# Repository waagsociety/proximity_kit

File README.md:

# Proximity Kit

This repo contains the documentation of the following projects:

* PK_MUV, developed as part of deliverable for the prject [MUV](https://www.muv2020.eu/)

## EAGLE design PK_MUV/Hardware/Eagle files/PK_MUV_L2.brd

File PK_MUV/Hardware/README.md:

# Parts
The PK_MUV kit is a portable device made of the following parts and features:

* Mcu/WiFi: Adafruit Feather HUZZAH esp8266 board
* NFC Reader: RC522 NFC reader
* Visual feedback: 3 WS1282 LEDs
* Audio feedback: buzzer
* Power switch
* Reset button
* Configuration button
* Indicator RGB Led for battery status
* Indicator RGB Led for configuration mode
* Indicator RGB Led for feedback
* Power supply: rechargeable battery or micro USB cable
* 6 mounting holes

The PK_MUV uses two off-the-shelf boards, the [Adafruit Feather HUZZAH esp8266](https://learn.adafruit.com/adafruit-feather-huzzah-esp8266/overview) and the NFC reader breakout board based on [MFRC522 chip](https://www.nxp.com/docs/en/data-sheet/MFRC522.pdf), and four boards made in the fablab, the PK_MUV pcb, the PK_MUV_L1 pcb, the PK_MUV_L2 pcb and the PK_MUV_sw pcb.

The boards are made using the small milling machine Roland Modela MDX-20, each pcbs require two jobs: mill the trace and cut/drill the boards, in the folder digital files you find the png machinable files.
Tools used:
- one side copper plate, FR1
- to mill the traces: endmill, 1/64inch diameter
- to cut and drill: endmill, 1/32inch diameter

The files used on the machine are in the folder [Machinable files](https://github.com/emmapa/proximity_kit/tree/master/PK_MUV/Tech/Machinable%20files).<br>
The original Eagle files are in the [Eagle files](https://github.com/emmapa/proximity_kit/tree/master/PK_MUV/Tech/Eagle%20files).

In Fablab Amsterdam the software to generate the rml file and send it to the machine is Fabmodules. It is highly recommended to use the last version of Fabmodules, aka mods http://mods.cba.mit.edu/; previous versions of fabmodules, still work but double check the output of the software before to send the job to the machine, in some cases the path is not well calculated.

In the image below you find the setting to engrave the traces, drill holes and cutout the board.
<br>

Note: when you mill the outlines, you will need to trick the fabmodules!! Some holes are two smalls to be identified with a diameter tool of 1/64inch (0.79248mm) so you can set the diameter tool to 0.78mm and all the holes will be milled; yes, you lose some copper on the pad but it is still enough to solder vias and components.

#### PK_MUV pcb

| top view  | bottom view |
| ------------- | ------------- |
|   |  |
| All the header are THT, pitch 2.54mm. <br> JP_LEDS: 1x3 female header, THT <br> JP_BUZ: holes for piezo<br> JP_SW: 2x2 male header<br> Feather header 1: 1x16 female header<br> Feather header 2: 1x16 female header<br> JP_LED_TAG: 1x4 female header<br> JP_NFC: 1x8 female header <br> | All the resistors are smd 1206. <br>R1: 1M Ohm<br> R2: 220k Ohm<br> R3: 0 Ohm<br> R4: 0 Ohm<br> R5: 10k Ohm<br> R6: 470 Ohm <br> R7: 0 Ohm<br>|
|   | |
|| 

**note**: the red traces are jumper wires placed on the top layer

#### PK_MUV_L1 pcb

| top view  | bottom view |
| ------------- | ------------- |
|   |  |
| The header is THT, pitch 2.54mm. <br> JP1: 1x04 male header 90° | Capacitors is smd 1206. <br>C1: 0.1uF <br> U1: WS2812B Led|
|   | |
|   | |

#### PK_MUV_L2 pcb

| top view  | bottom view |
| ------------- | ------------- |
|   |  |
| The header is THT, pitch 2.54mm. <br> JP1: 1x03 male header 90°   | Resistors and capacitors are smd 1206. <br>C1=C2: 0.1uF <br> U1=U2: WS2812B Led |
|   | |
|   | |

#### PK_MUV_sw pcb

| top View  | bottom view |
| ------------- | ------------- |
|   |  |
| sw1 = sw2: Tactile Switch THT | The header is smd, pitch 2.54mm <br> JP1: 2x2 male header<br> |
|   | |
||  |

### Battery cable
The switch power is inserted in the power wire of the battery.

Depending on the size of the case and the arrangements inside it, you could need to extend the power cable. This [tutorial](https://learn.adafruit.com/on-slash-off-switches) explains step-by-step how to wire the on/off switch, the material are part of the BOM.

### Assembly notes
#### Buzzer
On the PK_MUV pcb there two holes dedicated to the transducer element, depending on the model and the wires,  you can use both THT pads or just one.

#### Switches
The connection of the switches to the main board happens with two IDC connectors and a four wires flat cable.
It is important to plug the connectors in the right orientation, in the photos below you can see the alignment between the two boards.

#### General overview
The PK_MUV uses female/male header to attach the different boards but it works also using different settings.
You could solder all the components directly on the PK_MUV board to have a more compact and robust solution.
You could also use jumper wires to place the pcb far from the main pcb.

### BOM notes
Many items in the BOM can be bought only in minimum amount, when you actually are going to use one or two component. The total cost is therefore expressed as:
* total purchase: the cost of the purchase, buying the minimum amount per items
* cost of 1 kit: considering the cost of only the component used in the kit.

for example: if you buy the "feather header 1" from Farnell, you have to buy 10 components even if you are going to use only one. In the purchase cost the item "feather header 1" is 12€ but in the single cost of one kit, the item value is 1,2€.

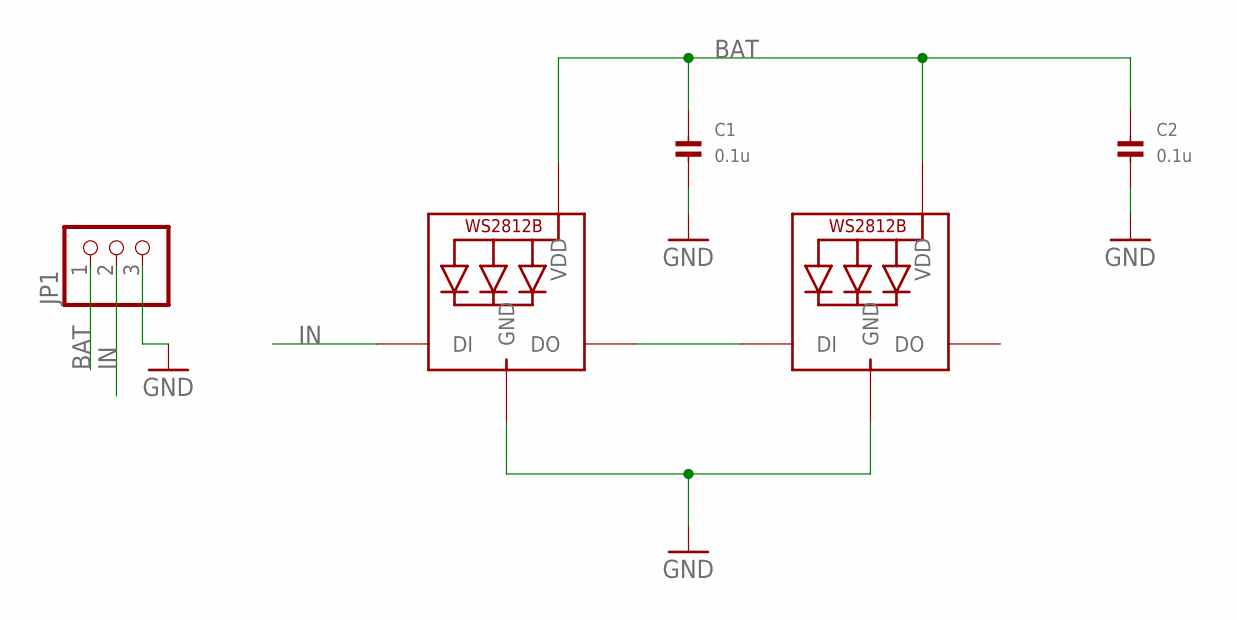
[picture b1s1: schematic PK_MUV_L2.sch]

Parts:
C1, C2: 0.1u; 1206
JP1: HEADER-1X3; 1X03_OVAL
LED1, LED2: WS2812B_5050N; WS2812B-NARROW

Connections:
BAT: C1.1, C2.1, JP1.1, LED1.1-VDD (VDD), LED2.1-VDD (VDD)
GND: C1.2, C2.2, JP1.3, LED1.3-GND (GND), LED2.3-GND (GND)
IN: JP1.2, LED1.4-DIN (DI)
unnamed: LED1.2-DOUT (DO), LED2.4-DIN (DI)

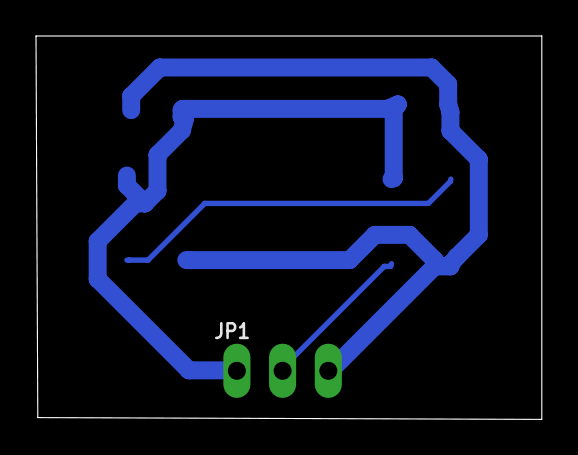
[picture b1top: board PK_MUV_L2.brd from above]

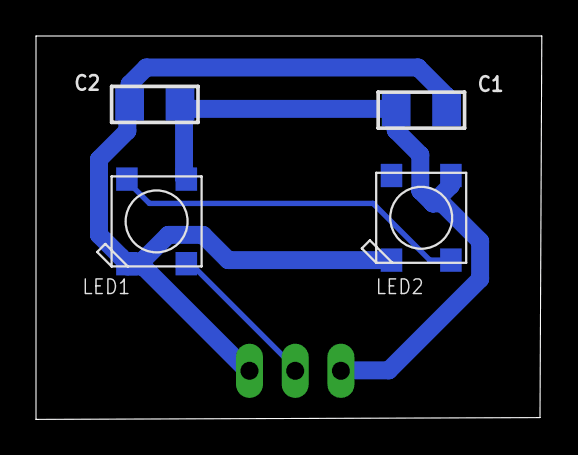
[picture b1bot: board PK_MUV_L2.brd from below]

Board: 2 copper layers, 28.1 x 21.3 mm, 5 parts (4 on the bottom side), 4 nets.

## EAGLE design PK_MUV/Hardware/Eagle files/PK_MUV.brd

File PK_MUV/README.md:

# PK_MUV

This page contains the description of the PK_MUV kit and the instructions to use it.<br>
In the Repo you also find:
* blocks diagram
* digital files to reproduce it, Eagle file and png files
* code
* BOM

The kit described in this Repo is about the electronics components and the firmware to realise the PK_MUV.

## Intro
The goal of the kit is to enable users of the application MUV, to identify proximity to strategic locations or routes, where the PK_MUV is located. The detection of proximity uses NFC technology and the user must be in possession of a [Tag_MUV](MUV-Tags) to properly use this feature of the app.
The PK_MUV is the device where the user can register proximity and it can be located in places important for the MUV project, for example: schools, offices, shops, parks, public services.

The PK_MUV is a WiFi module (esp8266) with NFC reader (RC522).
The PK_MUV kit is programmed to read [Tag_MUV](MUV-Tags). When the user operates the TAG_MUV on PK_MUV kit, the following informations are sent to the MUV server:
* Tag_MUV UID to identify the user
* PK_MUV ID to identify the location of the kit.<br>

The kit includes:
- Power slide switch: to turn on/off the kit when it runs on battery
- Reset switch: to reset the kit while it is operating
- Config switch: it is used to enter in configuration mode or run the check routine.
- Tag Led: rgb Led that gives feedback when a tag is detected by the reader, also called Tag routine.
- Config Led: rgb Led that gives feedback during the start-up and the check routines.
- Batt Led: rgb Led that visualise the battery status.

### Connect the PK_MUV to the local WiFi
Turn on the PK_MUV (ON/OFF switch). If the kit is not connected to the WiFi, the Config Led is on/blue, the kit is ready to be connected and it creates a network named MUV.
At this point you need a smartphone/tablet or computer, join the network MUV.

|| |
| ------------- | ------------- |

Automatically on the device you are using (smartphone/tablet/computer) the configuration window will pop-up.

|| |
| ------------- | ------------- |

If the window doesn't appear, open a browser and go to the address: http://192.168.4.1/.

Clicking on Info, you can see the information related to the kit and find the PK_MUV kit ID that in the window is called Chip ID.

Clicking on Configure WiFi, you are in the right place to connect the kit to you local WiFi.

Select the WiFi and type the password.
In the tag "Insert address", write the location of the kit.

Click save and the kit will be now connected, the Config Led blinks green and you are ready to use the kit.
It is also possible to enter in configuration mode manually, see the below section [configuration mode](Configuration-Mode).

### Modes and Routines/Messages
The operation of the PK_MUV can be described by modes and routine.
The modes are conditions in which the kit is waiting for some actions from the users:
* **configuration mode**: the kit is waiting to be connected to the local WiFi
* **operation mode**: the kit is operating and waiting to detect a Tag_MUV

The routines are a set of actions that the kit executes when it is triggered:
* **start-up routine**: it happens when the kit is powered-on or reset
* **tag routine**: it happens when the kit detect a tag
* **check routine**: it happens when the user need to check the functionality of the kit
The
<br>

#### Configuration Mode
Config Led : <br>
The kit is in configuration mode when it is not connected to the Local WiFi. In configuration mode the Config Led is steady blue.
You can manually enter in configuration mode with the following steps: keep pushed the Config switch and reset the kit. Hold the Config switch until the Config Led turns blue, the PK_MUV can to connected to the local Wifi, see previous [section](Connect-the-PK-MUV-to-the-local-WiFi).

**note**: you can also use configuration mode to change the WiFi Network at which the PK_MUV is connected.

#### Operation Mode
Config Led: <br>
If the kit has been successfully configured, it enters in operation mode.
The Tag Led and the Config Led are off, the NFC reader is ready to accept tags and the WiFi module is off to optimise the power consumption.
When the kit is operating and it has not been triggered by any tag, it will stay in operation mode.

#### Start-up routine
Config Led: <br>
When the kit is powered-on or reseted, it runs a sequence of test to verify the proper functionality.
It will connect to the local WiFi, it will verify the connection with the server MUV and it will send a start-up message. If the execution of the start-up routine is successful the Config Led blinks green light and the start-up message is sent to the MUV server:

{"message":"startup","id":1756474,"location":"Nieuwmarkt 4, Amsterdam","rssi":-52, "batt":50}

for details about the payload content, see [Uplinks](https://github.com/waagsociety/proximity_kit/tree/master/PK_MUV/Software#Uplinks).

#### Tag Routine
Tag Led : <br>
When the reader get a Tag_MUV, the Tag Led blinks three times, meaning:
* the kit received a tag and the tag is recognised as Tag_MUV
* the kit connected to the local WiFi
* the kit sent the MUV message to the MUV server

and the kit will send to the MUV the following payload:

{"id":1756474,"uid":"04:23:AB:32:EC:4C:81”}

for details about the payload content, see [Uplinks](https://github.com/waagsociety/proximity_kit/tree/master/PK_MUV/Software#Uplinks).

The color code of the Tag Led is:<br>
 : the tag doesn't have the credential of the MUV project.<br>
 : the tag was recognised as MUV, but the kit couldn't connect to the WiFi.<br>
 : the tag was recognised as MUV, it could connect to the WiFi but it couldn't reach the MUV server.

#### Check Routine
To execute the check routine, press once the Config Switch and you can verify the following features:
* battery level
* WiFi connection
* MUV server connectivity

The Batt Led will be steady for few seconds and the colour represents the battery level.<br>
The feedback of the routine is visualised on the Config Led:<br>
: the kit is operating properly and it will send the "check message".<br>
: the kit can't connect to the WiFi.<br>
: the kit can't reach the MUV server and the "check message" is not sent.

The message sent to the server is:<br>
{"message":"check","id":1756474,"location":"Nieuwmarkt 4, Amsterdam","rssi":-59,"batt”:50}<br>
for details about the payload content, see [Uplinks](https://github.com/waagsociety/proximity_kit/tree/master/PK_MUV/Software#Uplinks).

## Power supply and Battery Led
The PK_MUV kit runs on a rechargeable battery, a 2000mAh Lithium Ion Polymer cell last about 4 days when the PK_MUV kit works in operational mode. The status of the battery is visualised by the Batt Led:

* battery level >= 96%: Batt Led is steady on, green
* 20% > battery level >= 10%: Batt Led blinks, colour red.
* battery level < 10%: Batt Led is steady on, colour red.

When the battery is between 96% and 20%, the Batt Led stays off, and to know its level you need to execute the Check Routine. Colour scale used during Check routine:
*  100% > battery level >= 80%: Batt Led colour green
*  80% > battery level >= 60%: Batt Led green/yellow
*   60% > battery level >= 40%: Batt Led yellow.
*   40% > battery level >= 20%: Batt Led orange.
*  20%  battery level >= 0: Batt Led colour red.

When the Batt Led is red, the battery is almost empty. To recharge the internal battery you can use a micro USB cable and a +5V USB charger (the ones you use with phones are good), plug the cable to the USB port on the side of the kit. When the Batt Led is steady green, the battery is charged. While the kit is under charge, it still operates normally.

**Note**: when you charge the battery, be sure the power switch is ON otherwise the battery will not get charged.

You can run the PK_MUV kit without battery and use the USB cable to supply it. In this case it is recommended to disconnect the battery or leave the power switch in position OFF. In this setting, the Batt Led is steady off.<br>
**Note**: when the USB cable is plugged, the kit operated continuously.

## MUV Tags
The Tags that have been successfully tested are NTAG213 and NTAG203, they are manufactured in different shapes: key-chain, sticker, business card and bracelet.<br>
<p align="center">

 <br></p>
To be able to use a Tag with the PK_MUV kit, you have to write in the Tag the MUV password and transform it in a Tag_MUV. On [this page](https://www.wakdev.com/en/apps.html) you find a list of apps to write NFC Tags but you also need a device to actually write the tag; in some cases the phone can do the job but in some other cases, for example if you have an iPhone6, you have to adopt an external device. During the testing phase of the PK_MUV, the ACR122 writer has been used with the desktop version of the software NFC tools.

How to use the ACR122 with NFC tools: [link](https://www.wakdev.com/en/apps/nfc-tools-pc-mac.html) To have access to the key, see section [Contacts](Contacts).

## Known Issues

There are some known issues we are working on to improve the case:

- USB hole in case is not large enough for many sizes of USB connector
- The USB port could be closer to the wall of the case
- The buttons should be press fit into the case so that no glue is required
- There should be letters engraved above the buttons to be able to tell which one is which
- There should be 2 acrylic diffusers on the back side for the LEDs, one for each LED
- The NFC sensor should be moved as close to the front wall as possible to improve the connection when the battery is low.

## Troubleshooting
| Problem | Solution |
|---------| -------- |
| Config Led is on: purple <br> | The FS are formatted and The WiFi settings reseted. <br> The Feather esp8266 must be reprogrammed.  <br>See [Code](code) page. |
| Config Led is on: aqua <br> | The MUV server can't be reached. <br> Reset the Kit. <br> Check the MUV credentials saved in the code |
| Config Led is on: blue <br>  | The kit is in Configuration mode.<br> Ready to be connected to the Local WiFi: [how](#Connect-the-PK-MUV-to-the-local-WiFi)  |

## Contacts
To have access to the MUV password, please contact: stefano@waag.org <br>
If you have questions about the reproducion or making or code, you can use the issue format of the repo.

<br />This work is licensed under a <a rel="license" href="http://creativecommons.org/licenses/by-sa/4.0/">Creative Commons Attribution-ShareAlike 4.0 International License</a>.

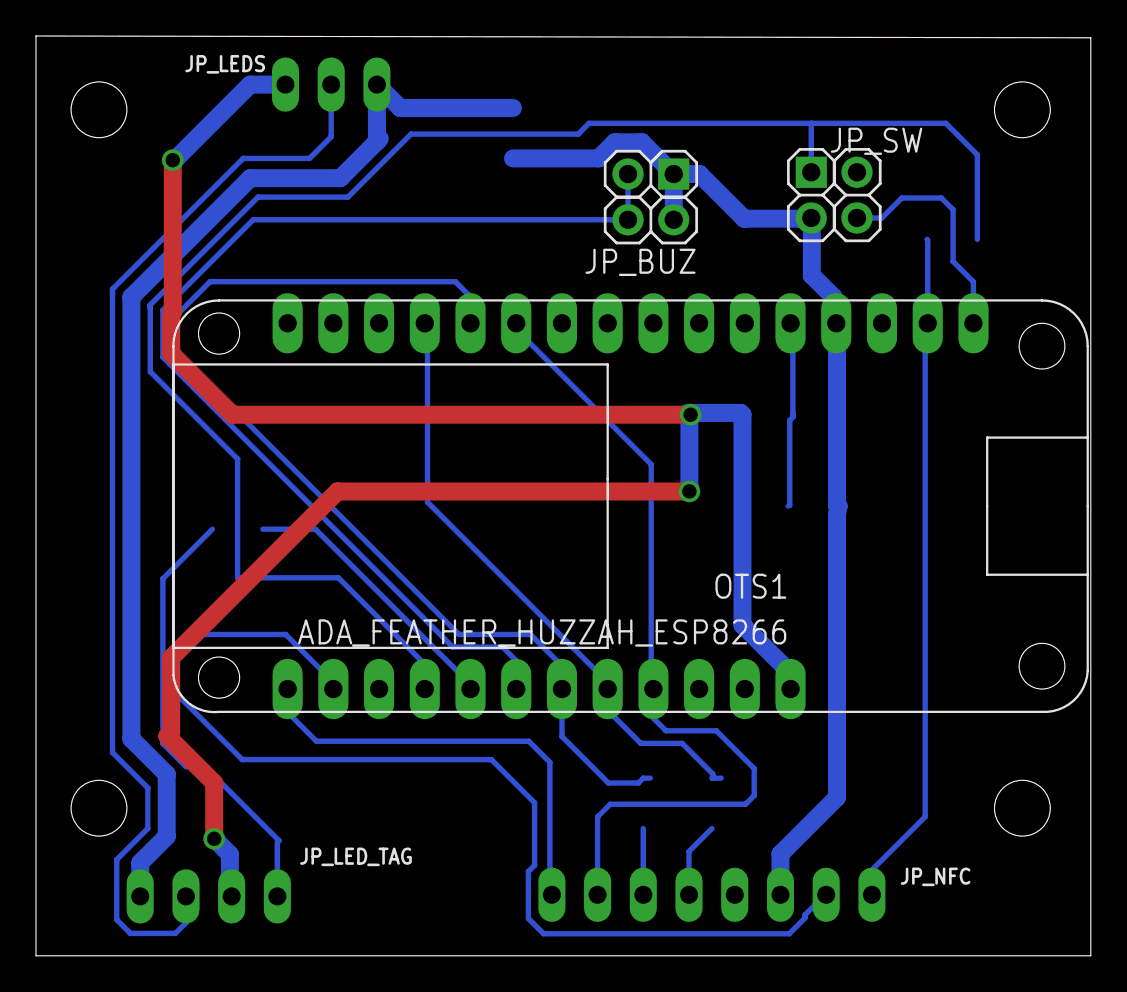
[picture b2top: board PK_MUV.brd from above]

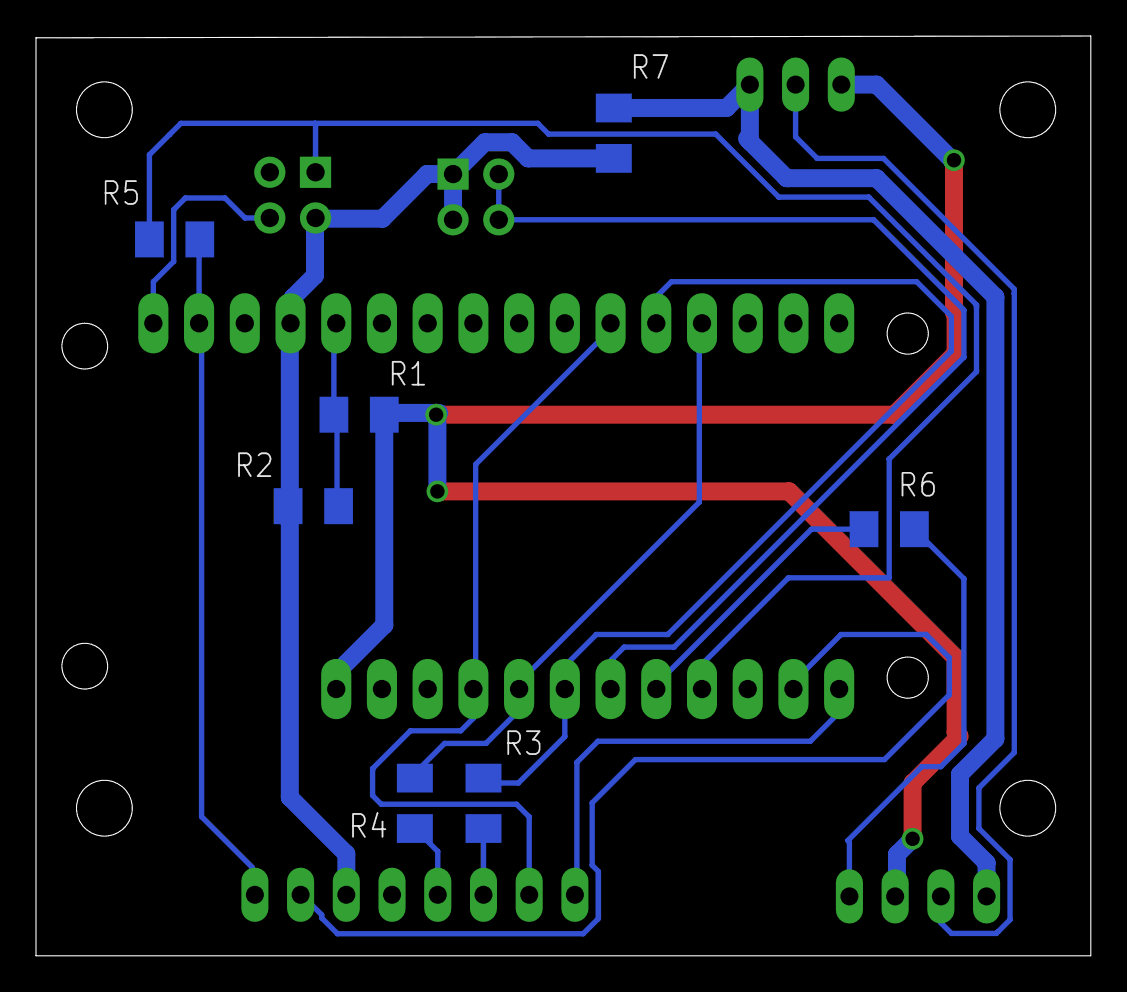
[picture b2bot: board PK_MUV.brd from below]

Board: 2 copper layers, 58.6 x 51.1 mm, 13 parts (7 on the bottom side), 15 nets.

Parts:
JP_BUZ: PINHD-2X2; 2X2
JP_LEDS: 1X03_OVAL
JP_LED_TAG: 1X04_OVAL
JP_NFC: 1X08_OVAL
JP_SW: PINHD-2X2; 2X2
OTS1: ADA_FEATHER_HUZZAH_ESP8266
R1: 1M; M1206
R2: 220K; M1206
R3, R4: M1206
R5: 10K; M1206
R6: 470; M1206
R7: 0; M1206

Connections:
+3V3: JP_NFC.8, OTS1.14, R5.2
BAT: JP_LEDS.3, JP_LED_TAG.3, OTS1.1, R1.2
BAT_LEV: OTS1.17, R1.1, R2.2
BUZ: JP_BUZ.3, JP_BUZ.4, OTS1.7
CONF: JP_SW.1, OTS1.9, R5.1
GND: JP_BUZ.1, JP_BUZ.2, JP_LEDS.1, JP_LED_TAG.1, JP_NFC.6, JP_SW.3, OTS1.16, R2.1, R7.1, R7.2
IN_LIGHT: JP_LED_TAG.4, R6.1
MISO: JP_NFC.4, OTS1.5, OTS1.25, R4.1, R4.2
MOSI: JP_NFC.3, OTS1.6, OTS1.24, R3.1, R3.2
unnamed: OTS1.8, R6.2
OUT_LIGHT: JP_LEDS.2, JP_LED_TAG.2
RST: JP_SW.4, OTS1.13
RST_NFC: JP_NFC.7, OTS1.11
SCK: JP_NFC.2, OTS1.4, OTS1.23
SDA: JP_NFC.1, OTS1.12

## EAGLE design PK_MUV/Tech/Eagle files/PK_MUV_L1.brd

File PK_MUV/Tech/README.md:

# Parts
The PK_MUV kit is a portable device made of the following parts and features:

* Mcu/WiFi: Adafruit Feather HUZZAH esp8266 board
* NFC Reader: RC522 NFC reader
* Visual feedback: 3 WS1282 LEDs
* Audio feedback: buzzer
* Power switch
* Reset button
* Configuration button
* Indicator RGB Led for battery status
* Indicator RGB Led for configuration mode
* Indicator RGB Led for feedback
* Power supply: rechargeable battery or micro USB cable
* 6 mounting holes

The PK_MUV uses two off-the-shelf boards, the Adafruit Feather HUZZAH esp8266 and the NFC reader RC522, and four boards made in the fablab, the PK_MUV pcb, the PK_MUV_L1 pcb, the PK_MUV_L2 pcb and the PK_MUV_sw pcb.

The boards are made using the small milling machine Roland Modela MDX-20, each pcbs require two jobs: mill the trace and cut/drill the boards, in the folder digital files you find the png machinable files.
Tools used:
- one side copper plate, FR1
- to mill the traces: endmill, 0,4mm diameter
- to cut and drill: endmill, 1/64 inch diameter

The files used on the machine are in the folder [Machinable files](https://github.com/emmapa/proximity_kit/tree/master/PK_MUV/Tech/Machinable%20files).<br>
The original Eagle files are in the [Eagle files](https://github.com/emmapa/proximity_kit/tree/master/PK_MUV/Tech/Eagle%20files).

#### PK_MUV pcb

| top view  | bottom view |
| ------------- | ------------- |
|   |  |
| All the header are THT, pitch 2.54mm. <br> JP_LEDS: 1x3 female header, THT <br> JP_BUZ: holes for piezo<br> JP_SW: 2x2 male header<br> Feather header 1: 1x16 female header<br> Feather header 2: 1x16 female header<br> JP_LED_TAG: 1x4 female header<br> JP_NFC: 1x8 female header <br> | All the resistors are smd 1206. <br>R1: 1M Ohm<br> R2: 220k Ohm<br> R3: 0 Ohm<br> R4: 0 Ohm<br> R5: 10k Ohm<br> R6: 470 Ohm <br> R7: 0 Ohm<br>|
|   | |
|| 

**note**: the red traces are jumper wires placed on the top layer

#### PK_MUV_L1 pcb

| top view  | bottom view |
| ------------- | ------------- |
|   |  |
| The header is THT, pitch 2.54mm. <br> JP1: 1x04 male header 90° | Capacitors is smd 1206. <br>C1: 0.1uF <br> U1: WS2812B Led|
|   | |
|   | |

#### PK_MUV_L2 pcb

| top view  | bottom view |
| ------------- | ------------- |
|   |  |
| The header is THT, pitch 2.54mm. <br> JP1: 1x03 male header 90°   | Resistors and capacitors are smd 1206. <br>C1=C2: 0.1uF <br> U1=U2: WS2812B Led |
|   | |
|   | |

#### PK_MUV_sw pcb

| top View  | bottom view |
| ------------- | ------------- |
|   |  |
| sw1 = sw2: Tactile Switch THT | The header is smd, pitch 2.54mm <br> JP1: 2x2 male header<br> |
|   | |
||  |

### Battery cable

### Assembly note
##### Buzzer
On the PK_MUV pcb there two holes dedicated to the transducer element, depending on the model you can use both THT pads or just one.

IMMAGINE PIEZO 1<br>
IMMAGINE PIEZO 2

##### Switches
The connection of the switches to the main board happens with two IDC connectors and a four wires flat cable.
It is important to plug the connectors in the right orientation, in the photos below you can see the alignment between the two boards.

#### General overview
The PK_MUV uses female/male header to attach the different boards but it works also using different settings.
You could solder all the components directly on the PK_MUV board to have a more compact and robust solution.
You could also use Jumper wires to place the pcb far from the main pcb.

### BOM notes
Many items in the BOM can be bought only in minimum amount, when you actually are going to use one or two component. The total cost is therefore expressed as:
* total purchase: the cost of the purchase, buying the minimum amount per items
* cost of 1 kit: considering the cost of only the component used in the kit.

for example: if you buy the "feather header 1" from Farnell, you have to buy 10 components even if you are going to use only one. In the purchase cost the item "feather header 1" is 12€ but in the single cost of one kit, the item value is 1,2€.

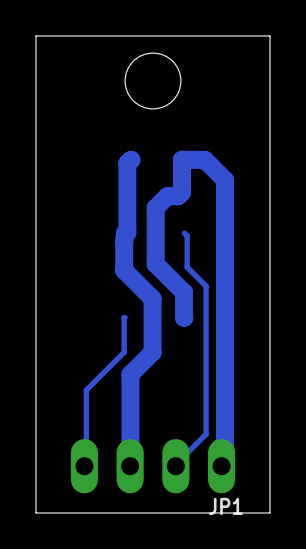
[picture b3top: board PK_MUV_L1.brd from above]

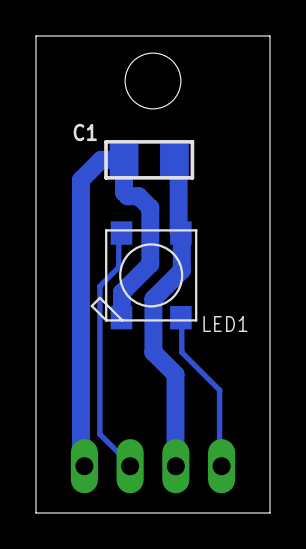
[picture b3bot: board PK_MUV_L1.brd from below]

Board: 2 copper layers, 13.0 x 26.5 mm, 3 parts (2 on the bottom side), 4 nets.

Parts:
C1: 0.1u; 1206
JP1: 1X04_OVAL
LED1: WS2812B_5050N; WS2812B-NARROW

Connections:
BAT: C1.1, JP1.3, LED1.1-VDD
GND: C1.2, JP1.1, LED1.3-GND
IN_LIGHT: JP1.4, LED1.4-DIN
OUT_LIGHT: JP1.2, LED1.2-DOUT

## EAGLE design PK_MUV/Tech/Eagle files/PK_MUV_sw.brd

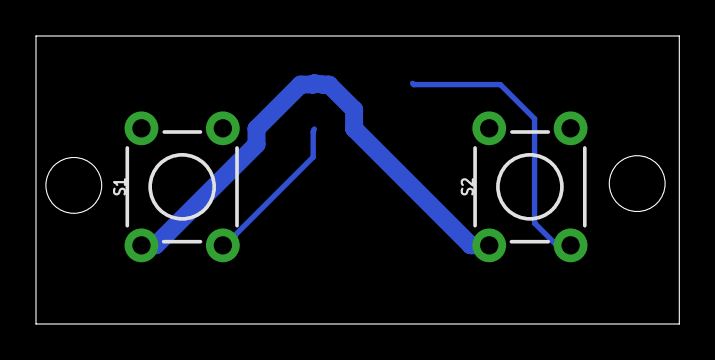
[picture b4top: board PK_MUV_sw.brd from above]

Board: 2 copper layers, 35.7 x 16.0 mm, 3 parts (1 on the bottom side), 3 nets.

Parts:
JP1: PINHD-2X2-SMD; 2X02SMD
S1, S2: MOMENTARY-SWITCH-SPST-PTH-6.0MM-KIT; TACTILE_SWITCH_PTH_6.0MM_KIT

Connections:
CONF: JP1.1, S1.3
GND: JP1.3, S1.1, S2.1
RST: JP1.4, S2.3

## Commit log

2018-12-06 update batt
2018-12-06 .DS_Store banished!
2018-12-13 license
2019-01-07 Adding case files
2019-01-07 Move files
2019-01-07 rename directory
2019-01-07 Fix broken link, reformat and attribution
2019-03-19 update image production
2019-03-19 clean double text
2019-03-19 New version for the assembling of the case
2019-03-28 fix bom machinable file

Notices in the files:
PK_MUV/README.md:
This work is licensed under a Creative Commons Attribution-ShareAlike 4.0 International License.
parts and their libraries:
microbuilder: This work is placed in the public domain, and may be freely used for commercial and non-commercial work with the following conditions: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
SparkFun-Switches: Licensing: Creative Commons ShareAlike 4.0 International - https://creativecommons.org/licenses/by-sa/4.0
